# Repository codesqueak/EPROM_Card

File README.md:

# NAS-GEM-80 EPROM CARD Version 2.3

This card has been designed to replace the use of 2708/2716 EPROM’s with the more readily available and simpler to program 2732 / 2764 devices.

## Introduction

The board support up 5 devices or 4 devices and the original 8K Basic ROM. Both a 2732/2764 EPROM and the Basic ROM may be present on the card simultaneously, with the active device being selected via a switch

Each device may be decoded to any 4K boundary, with a typical configuration being:

* 2732 decoded to D000 for NAS-DOS
* 2732 decoded to C000 for NAS-DIS & NAS-DEBUG
* 2764 decoded to E000 / F000 for 8K BASIC

The card also supports the Nascom Page Mode functionality, with any of the four pages being selectable via a DIL switch. If page 0 is selected then the card will be enabled at power up / reset.

The Page Mode functionality may also be disabled if required via a switch selection

NAS I/O selection is available via a link/switch.  This allows I/O on a Nascom to function correctly
M. EXT is supported for Nascom 1 usage.  This is selectable via a link

If the original 8K Basic ROM is being used, be aware that no wait states are generated on this card. Some slow devices may not function correctly without the use of wait states.

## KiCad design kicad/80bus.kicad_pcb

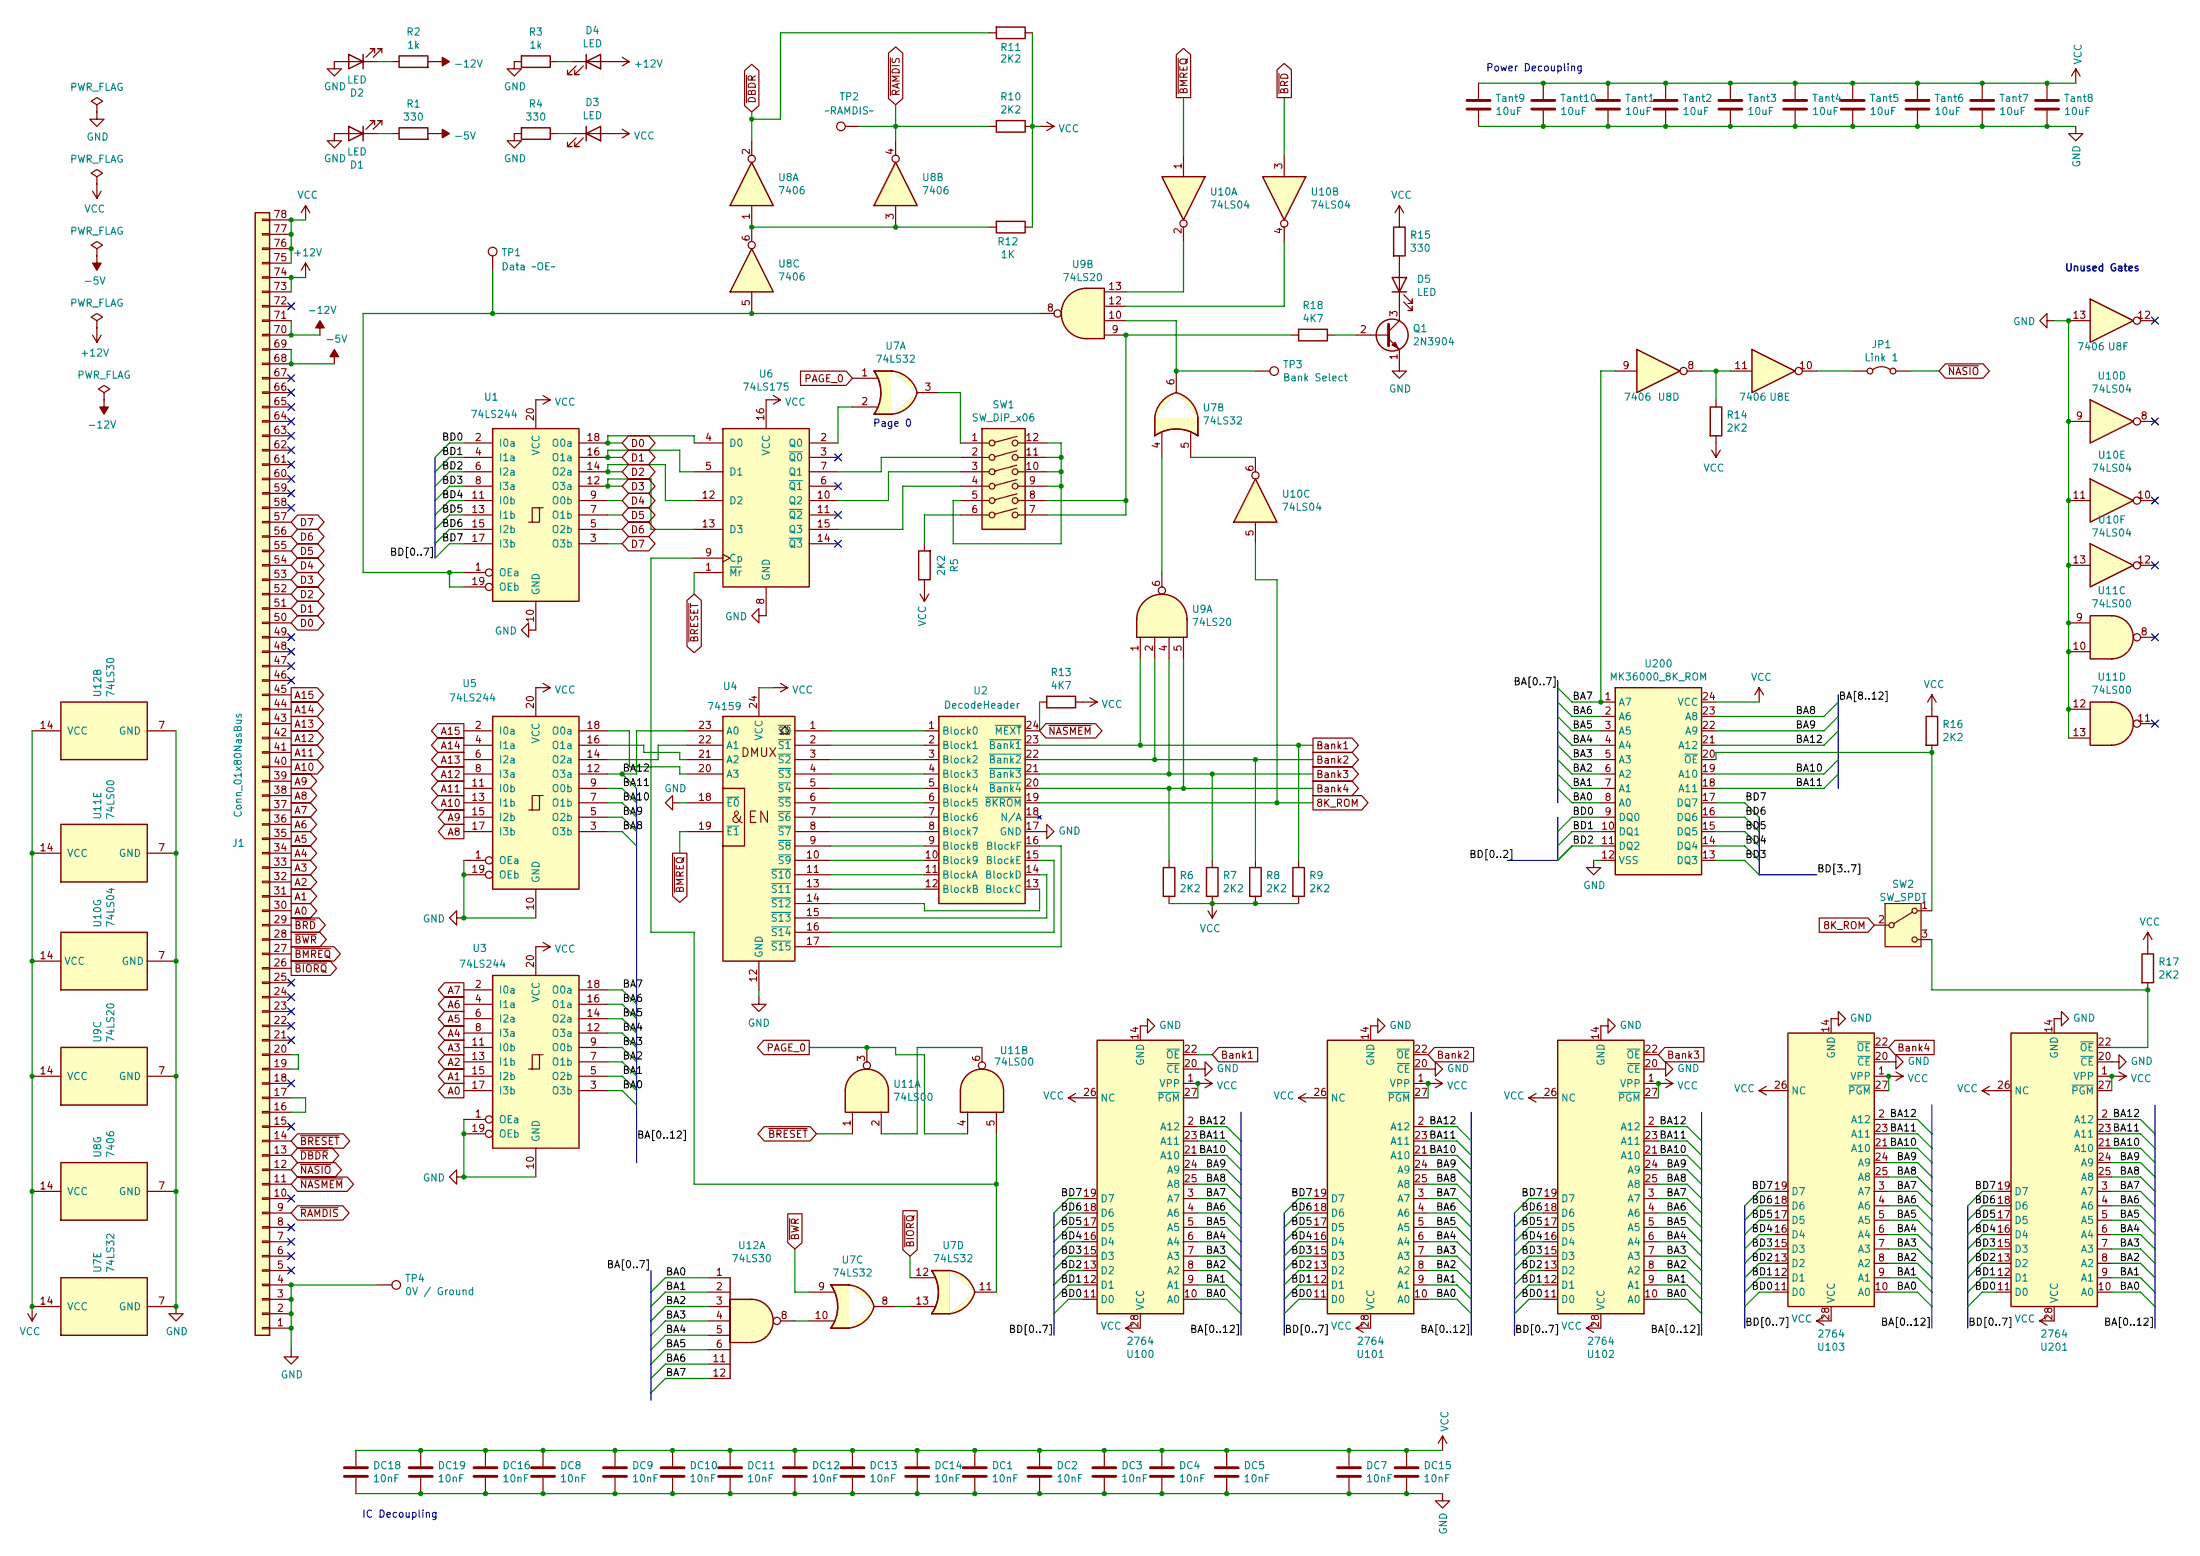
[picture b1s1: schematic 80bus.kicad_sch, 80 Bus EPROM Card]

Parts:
D1, D2, D3, D4, D5: LED; LED_D3.0mm
DC1, DC2, DC3, DC4, DC5, DC7, DC8, DC9, DC10, DC11, DC12, DC13, DC14, DC15, DC16, DC18, DC19: 10nF; C_Disc_D3.4mm_W2.1mm_P2.50mm
J1: Conn_01x80NasBus; 80BusEdgeConnector
JP1: Link 1; SW_DIP_SPSTx01_Slide_6.7x4.1mm_W7.62mm_P2.54mm_LowProfile
Q1: 2N3904; TO-92_Inline_Wide
R1, R4, R15: 330; R_Axial_DIN0309_L9.0mm_D3.2mm_P12.70mm_Horizontal
R2, R3: 1k; R_Axial_DIN0309_L9.0mm_D3.2mm_P12.70mm_Horizontal
R5, R6, R7, R8, R9, R10, R11, R14, R16, R17: 2K2; R_Axial_DIN0309_L9.0mm_D3.2mm_P12.70mm_Horizontal
R12: 1K; R_Axial_DIN0309_L9.0mm_D3.2mm_P12.70mm_Horizontal
R13, R18: 4K7; R_Axial_DIN0309_L9.0mm_D3.2mm_P12.70mm_Horizontal
SW1: SW_DIP_x06; DIP-12_W7.62mm_Socket
SW2: SW_SPDT; PinHeader_1x03_P2.54mm_Vertical
TP1: Data ~OE~; TestPoint_THTPad_D1.5mm_Drill0.7mm
TP2: ~RAMDIS~; TestPoint_THTPad_D1.5mm_Drill0.7mm
TP3: Bank Select; TestPoint_THTPad_D1.5mm_Drill0.7mm
TP4: 0V / Ground; TestPoint_THTPad_D1.5mm_Drill0.7mm
Tant1, Tant2, Tant3, Tant4, Tant5, Tant6, Tant7, Tant8, Tant9, Tant10: 10uF; C_Disc_D5.0mm_W2.5mm_P5.00mm
U1, U3, U5: 74LS244; DIP-20_W7.62mm_Socket
U2: DecodeHeader; DIP-24_W15.24mm
U4: 74159; DIP-24_W15.24mm_Socket
U6: 74LS175; DIP-16_W7.62mm_Socket
U7: 74LS32; DIP-14_W7.62mm_Socket
U8: 7406; DIP-14_W7.62mm_Socket
U9: 74LS20; DIP-14_W7.62mm_Socket
U10: 74LS04; DIP-14_W7.62mm_Socket
U11: 74LS00; DIP-14_W7.62mm_Socket
U12: 74LS30; DIP-14_W7.62mm_Socket
U100, U101, U102, U103, U201: 2764; DIP-28_W15.24mm
U200: MK36000_8K_ROM; DIP-24_W15.24mm

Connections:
8K_ROM: SW2.2 (B), U2.19 (~8KROM), U10.5
+12V: D4.2 (A), J1.73 (Pin_73_+12v), J1.74 (Pin_74_+12v)
-5V: J1.68 (Pin_68_-5v), J1.69 (Pin_69_-5v), R1.2
-12V: J1.70 (Pin_70_-12v), J1.71 (Pin_71_-12v), R2.2
/BA0: U3.3 (O3b), U12.1, U100.10 (A0), U101.10 (A0), U102.10 (A0), U103.10 (A0), U200.8 (A0), U201.10 (A0)
/BA1: U3.5 (O2b), U12.2, U100.9 (A1), U101.9 (A1), U102.9 (A1), U103.9 (A1), U200.7 (A1), U201.9 (A1)
/BA2: U3.7 (O1b), U12.3, U100.8 (A2), U101.8 (A2), U102.8 (A2), U103.8 (A2), U200.6 (A2), U201.8 (A2)
/BA3: U3.9 (O0b), U12.4, U100.7 (A3), U101.7 (A3), U102.7 (A3), U103.7 (A3), U200.5 (A3), U201.7 (A3)
/BA4: U3.12 (O3a), U12.5, U100.6 (A4), U101.6 (A4), U102.6 (A4), U103.6 (A4), U200.4 (A4), U201.6 (A4)
/BA5: U3.14 (O2a), U12.6, U100.5 (A5), U101.5 (A5), U102.5 (A5), U103.5 (A5), U200.3 (A5), U201.5 (A5)
/BA6: U3.16 (O1a), U12.11, U100.4 (A6), U101.4 (A6), U102.4 (A6), U103.4 (A6), U200.2 (A6), U201.4 (A6)
/BA7: U3.18 (O0a), U8.9, U12.12, U100.3 (A7), U101.3 (A7), U102.3 (A7), U103.3 (A7), U200.1 (A7), U201.3 (A7)
/BA8: U5.3 (O3b), U100.25 (A8), U101.25 (A8), U102.25 (A8), U103.25 (A8), U200.23 (A8), U201.25 (A8)
/BA9: U5.5 (O2b), U100.24 (A9), U101.24 (A9), U102.24 (A9), U103.24 (A9), U200.22 (A9), U201.24 (A9)
/BA10: U5.7 (O1b), U100.21 (A10), U101.21 (A10), U102.21 (A10), U103.21 (A10), U200.19 (A10), U201.21 (A10)
/BA11: U5.9 (O0b), U100.23 (A11), U101.23 (A11), U102.23 (A11), U103.23 (A11), U200.18 (A11), U201.23 (A11)
/BA12: U4.23 (A0), U5.12 (O3a), U100.2 (A12), U101.2 (A12), U102.2 (A12), U103.2 (A12), U200.21 (A12), U201.2 (A12)
/BD0: U1.2 (I0a), U100.11 (D0), U101.11 (D0), U102.11 (D0), U103.11 (D0), U200.9 (DQ0), U201.11 (D0)
/BD1: U1.4 (I1a), U100.12 (D1), U101.12 (D1), U102.12 (D1), U103.12 (D1), U200.10 (DQ1), U201.12 (D1)
/BD2: U1.6 (I2a), U100.13 (D2), U101.13 (D2), U102.13 (D2), U103.13 (D2), U200.11 (DQ2), U201.13 (D2)
/BD3: U1.8 (I3a), U100.15 (D3), U101.15 (D3), U102.15 (D3), U103.15 (D3), U200.13 (DQ3), U201.15 (D3)
/BD4: U1.11 (I0b), U100.16 (D4), U101.16 (D4), U102.16 (D4), U103.16 (D4), U200.14 (DQ4), U201.16 (D4)
/BD5: U1.13 (I1b), U100.17 (D5), U101.17 (D5), U102.17 (D5), U103.17 (D5), U200.15 (DQ5), U201.17 (D5)
/BD6: U1.15 (I2b), U100.18 (D6), U101.18 (D6), U102.18 (D6), U103.18 (D6), U200.16 (DQ6), U201.18 (D6)
/BD7: U1.17 (I3b), U100.19 (D7), U101.19 (D7), U102.19 (D7), U103.19 (D7), U200.17 (DQ7), U201.19 (D7)
A0: J1.30, U3.17 (I3b)
A1: J1.31, U3.15 (I2b)
A2: J1.32, U3.13 (I1b)
A3: J1.33, U3.11 (I0b)
A4: J1.34, U3.8 (I3a)
A5: J1.35, U3.6 (I2a)
A6: J1.36, U3.4 (I1a)
A7: J1.37, U3.2 (I0a)
A8: J1.38, U5.17 (I3b)
A9: J1.39, U5.15 (I2b)
A10: J1.40, U5.13 (I1b)
A11: J1.41, U5.11 (I0b)
A12: J1.42, U5.8 (I3a)
A13: J1.43, U5.6 (I2a)
A14: J1.44, U5.4 (I1a)
A15: J1.45, U5.2 (I0a)
Bank1: R9.1, U2.23 (~Bank1), U9.1, U100.22 (~OE)
Bank2: R8.1, U2.22 (~Bank2), U9.2, U101.22 (~OE)
Bank3: R7.1, U2.21 (~Bank3), U9.4, U102.22 (~OE)
Bank4: R6.1, U2.20 (~Bank4), U9.5, U103.22 (~OE)
D0: J1.50, U1.18 (O0a), U6.4 (D0)
D1: J1.51, U1.16 (O1a), U6.5 (D1)
D2: J1.52, U1.14 (O2a), U6.12 (D2)
D3: J1.53, U1.12 (O3a), U6.13 (D3)
D4: J1.54, U1.9 (O0b)
D5: J1.55, U1.7 (O1b)
D6: J1.56, U1.5 (O2b)
D7: J1.57, U1.3 (O3b)
GND: D1.2 (A), D2.2 (A), DC1.2, DC2.2, DC3.2, DC4.2, DC5.2, DC7.2, DC8.2, DC9.2, DC10.2, DC11.2, DC12.2, DC13.2, DC14.2, DC15.2, DC16.2, DC18.2, DC19.2, J1.1 (Pin_1_0v), J1.2 (Pin_2_0v), J1.3 (Pin_3_0v), J1.4 (Pin_4_0v), Q1.1 (E), R3.2, R4.2, TP4.1, Tant1.2, Tant2.2, Tant3.2, Tant4.2, Tant5.2, Tant6.2, Tant7.2, Tant8.2, Tant9.2, Tant10.2, U1.10 (GND), U2.17 (GND), U3.1 (OEa), U3.10 (GND), U3.19 (OEb), U4.12 (GND), U4.18 (~E0), U5.1 (OEa), U5.10 (GND), U5.19 (OEb), U6.8 (GND), U7.7 (GND), U8.7 (GND), U8.13, U9.7 (GND), U10.7 (GND), U10.9, U10.11, U10.13, U11.7 (GND), U11.9, U11.10, U11.12, U11.13, U12.7 (GND), U100.14 (GND), U100.20 (~CE), U101.14 (GND), U101.20 (~CE), U102.14 (GND), U102.20 (~CE), U103.14 (GND), U103.20 (~CE), U200.12 (VSS), U201.14 (GND), U201.20 (~CE)
unnamed: D1.1 (K), R1.1
unnamed: D2.1 (K), R2.1
unnamed: D3.1 (K), R4.1
unnamed: D4.1 (K), R3.1
unnamed: D5.2 (A), R15.2
unnamed: D5.1 (K), Q1.3 (C)
unnamed: J1.16, J1.17
unnamed: J1.19, J1.20
unnamed: JP1.1 (A), U8.10
unnamed: Q1.2 (B), R18.1
unnamed: R5.2, SW1.6
unnamed: R12.2, U8.1, U8.3, U8.6
unnamed: R14.1, U8.8, U8.11
unnamed: R18.2, SW1.7, SW1.8, U9.9
unnamed: SW1.1, U7.3
unnamed: SW1.5, SW1.9, SW1.10, SW1.11, SW1.12
unnamed: R16.2, SW2.1 (A), U200.20 (~OE)
unnamed: R17.2, SW2.3 (C), U201.22 (~OE)
unnamed: TP3.1, U7.6, U9.10
unnamed: TP1.1, U1.1 (OEa), U1.19 (OEb), U8.5, U9.8
unnamed: U2.1 (Block0), U4.1 (~S0)
unnamed: U2.2 (Block1), U4.2 (~S1)
unnamed: U2.3 (Block2), U4.3 (~S2)
unnamed: U2.4 (Block3), U4.4 (~S3)
unnamed: U2.5 (Block4), U4.5 (~S4)
unnamed: U2.6 (Block5), U4.6 (~S5)
unnamed: U2.7 (Block6), U4.7 (~S6)
unnamed: U2.8 (Block7), U4.8 (~S7)
unnamed: U2.9 (Block8), U4.9 (~S8)
unnamed: U2.10 (Block9), U4.10 (~S9)
unnamed: U2.11 (BlockA), U4.11 (~S10)
unnamed: U2.12 (BlockB), U4.13 (~S11)
unnamed: U2.13 (BlockC), U4.14 (~S12)
unnamed: U2.14 (BlockD), U4.15 (~S13)
unnamed: U2.15 (BlockE), U4.16 (~S14)
unnamed: U2.16 (BlockF), U4.17 (~S15)
unnamed: U4.22 (A1), U5.14 (O2a)
unnamed: U4.21 (A2), U5.16 (O1a)
unnamed: U4.20 (A3), U5.18 (O0a)
unnamed: U6.9 (Cp), U7.11, U11.5
unnamed: U6.2 (Q0), U7.2
unnamed: SW1.2, U6.7 (Q1)
unnamed: SW1.3, U6.10 (Q2)
unnamed: SW1.4, U6.15 (Q3)
unnamed: U7.4, U9.6
unnamed: U7.8, U7.13
unnamed: U9.13, U10.2
unnamed: U9.12, U10.4
unnamed: U7.5, U10.6
unnamed: U11.2, U11.6
unnamed: U7.10, U12.8
PAGE_0: U7.1, U11.3, U11.4
VCC: D3.2 (A), DC1.1, DC2.1, DC3.1, DC4.1, DC5.1, DC7.1, DC8.1, DC9.1, DC10.1, DC11.1, DC12.1, DC13.1, DC14.1, DC15.1, DC16.1, DC18.1, DC19.1, J1.75 (Pin_75_+5v), J1.76 (Pin_76_+5v), J1.77 (Pin_77__+5v), J1.78 (Pin_78__+5v), R5.1, R6.2, R7.2, R8.2, R9.2, R10.1, R11.1, R12.1, R13.1, R14.2, R15.1, R16.1, R17.1, Tant1.1, Tant2.1, Tant3.1, Tant4.1, Tant5.1, Tant6.1, Tant7.1, Tant8.1, Tant9.1, Tant10.1, U1.20 (VCC), U3.20 (VCC), U4.24 (VCC), U5.20 (VCC), U6.16 (VCC), U7.14 (VCC), U8.14 (VCC), U9.14 (VCC), U10.14 (VCC), U11.14 (VCC), U12.14 (VCC), U100.1 (VPP), U100.26 (NC), U100.27 (~PGM), U100.28 (VCC), U101.1 (VPP), U101.26 (NC), U101.27 (~PGM), U101.28 (VCC), U102.1 (VPP), U102.26 (NC), U102.27 (~PGM), U102.28 (VCC), U103.1 (VPP), U103.26 (NC), U103.27 (~PGM), U103.28 (VCC), U200.24 (VCC), U201.1 (VPP), U201.26 (NC), U201.27 (~PGM), U201.28 (VCC)
~BIORQ: J1.26, U7.12
~BMREQ: J1.27, U4.19 (~E1), U10.1
~BRD: J1.29, U10.3
~BRESET: J1.14, U6.1 (~Mr), U11.1
~BWR: J1.28, U7.9
~DBDR: J1.13, R11.2, U8.2
~NASIO: J1.12, JP1.2 (B)
~NASMEM: J1.11, R13.2, U2.24 (~MEXT)
~RAMDIS: J1.9, R10.2, TP2.1, U8.4

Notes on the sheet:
Power Decoupling
IC Decoupling
Unused Gates
Page 0

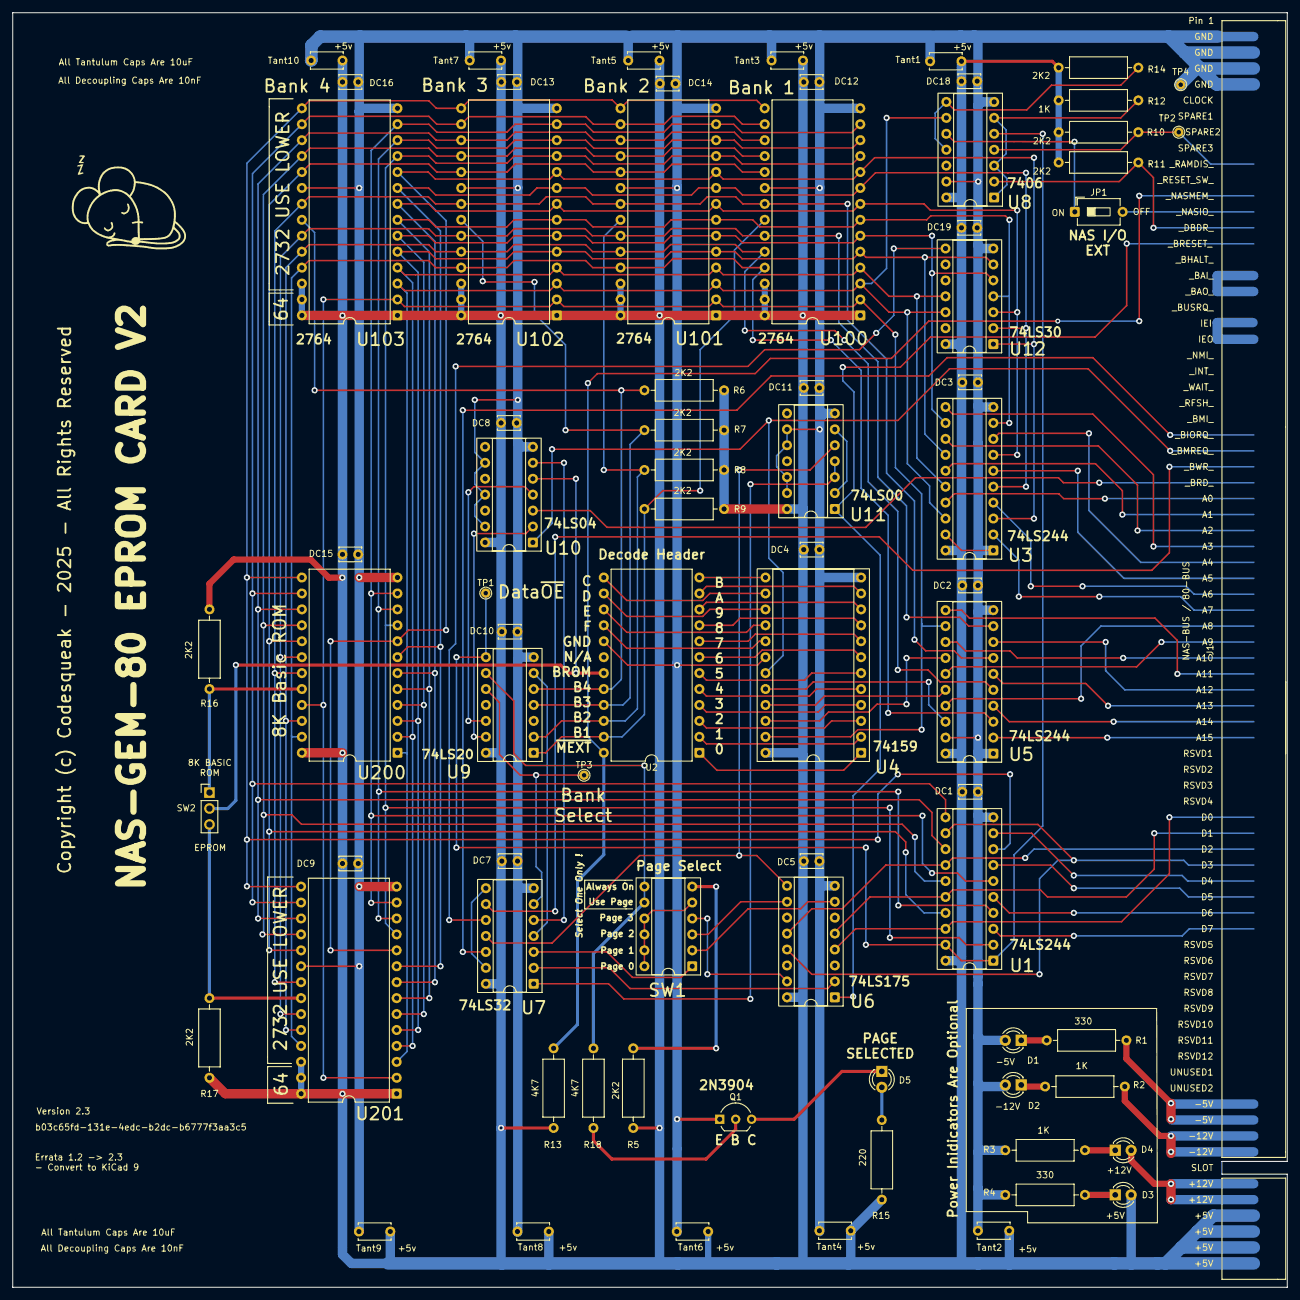
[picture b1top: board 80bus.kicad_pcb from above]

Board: 2 copper layers, 203.2 x 203.2 mm, 79 parts (1 on the bottom side), 116 nets.

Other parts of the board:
G1: LOGO; sleepymouse_small
G001: LOGO; qr-code

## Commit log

2023-06-23 Initial file drop
2023-06-23 Remove unsed files
2023-06-23 Move files
2023-06-23 Remove unused file
2023-08-26 pdf docs
2025-04-16 Update docs

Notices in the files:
kicad/80bus.kicad_pcb:
Copyright (c) Codesqueak - 2025 - All Rights Reserved
